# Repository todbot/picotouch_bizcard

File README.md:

# picotouch_bizcard

Business card-sized (2"x1.5") USB / MIDI touch controller

video demo on youtube: https://www.youtube.com/watch?v=1QFjxGo58Xc

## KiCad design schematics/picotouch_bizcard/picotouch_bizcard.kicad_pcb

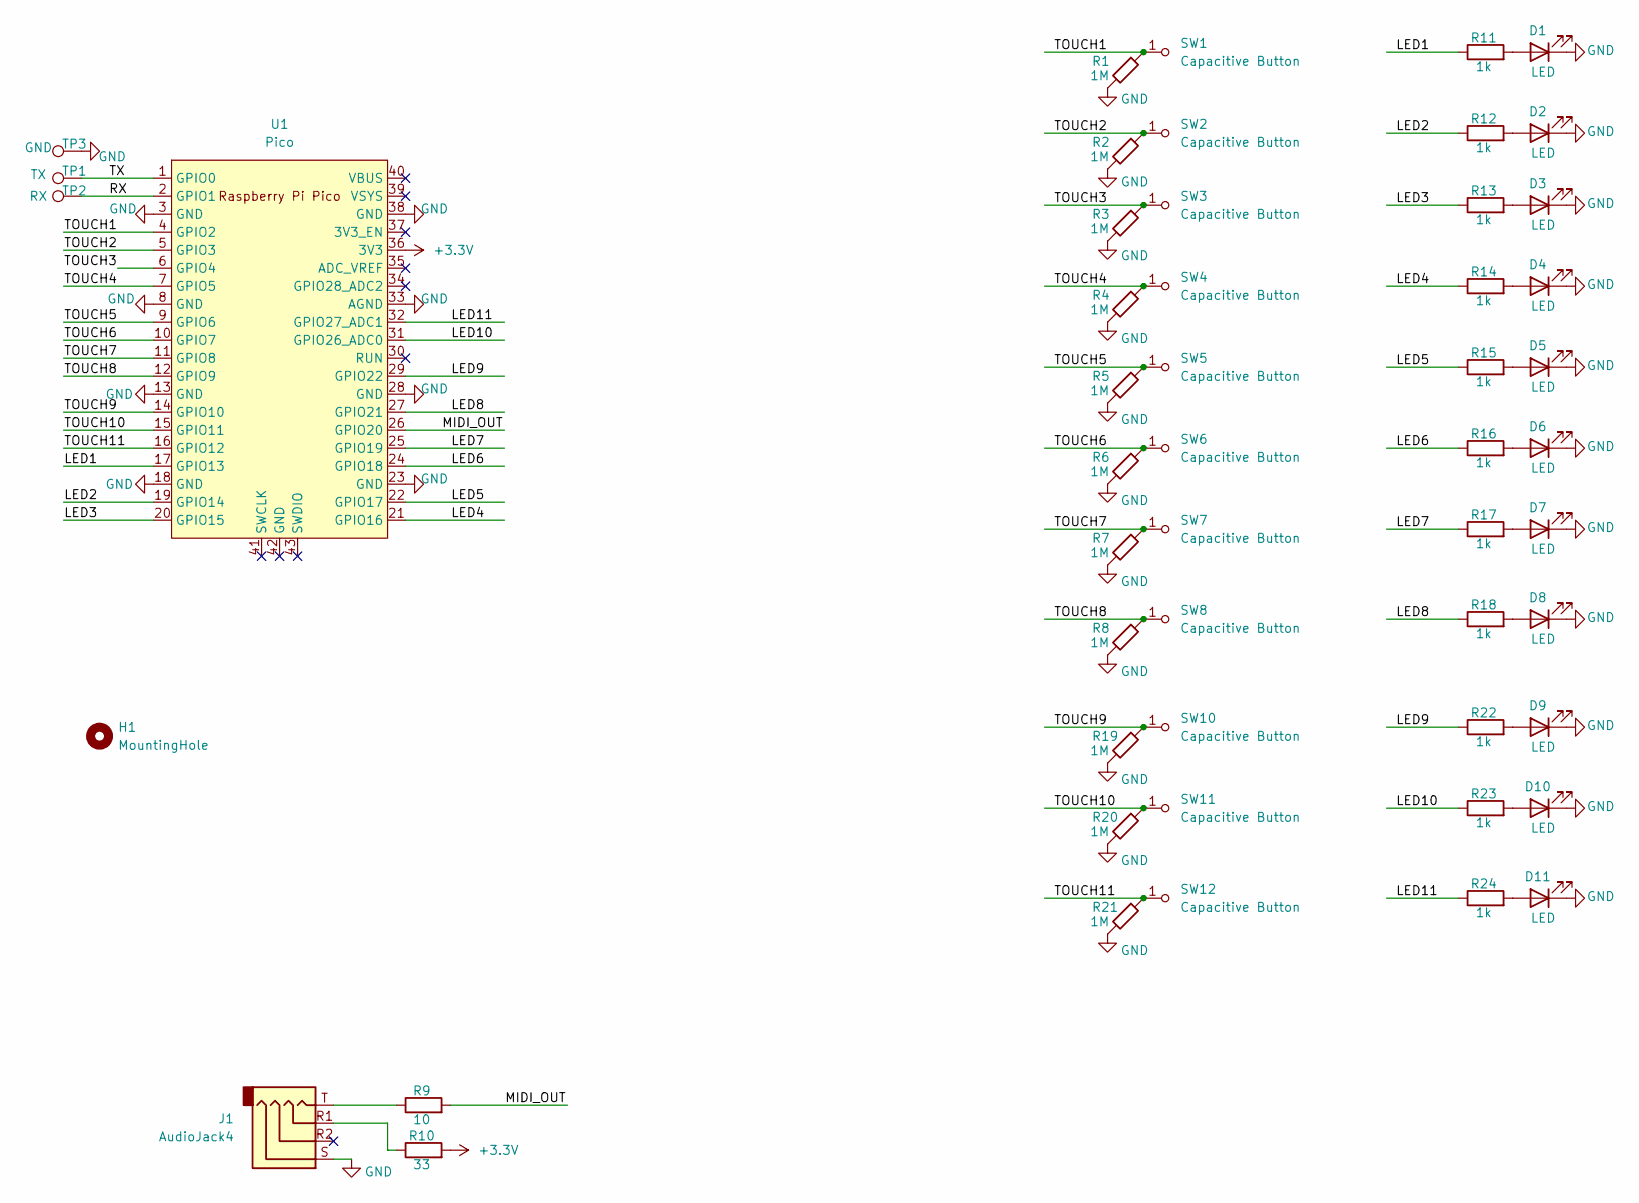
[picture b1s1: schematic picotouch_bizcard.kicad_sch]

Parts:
D1, D2, D3, D4, D5, D6, D7, D8, D9, D10, D11: LED; LED1206_LTST-C230KRKT-cutout; LCSC C125107
H1: MountingHole; MountingHole_2.5mm
J1: AudioJack4; Jack_3.5mm_PJ320D_Horizontal
R1, R2, R3, R4, R5, R6, R7, R8, R19, R20, R21: 1M; R_0603_1608Metric
R9: 10; R_0603_1608Metric
R10: 33; R_0603_1608Metric
R11, R12, R13, R14, R15, R16, R17, R18, R22, R23, R24: 1k; R_0603_1608Metric
SW1, SW2, SW3, SW4, SW5, SW6, SW7, SW8, SW10, SW11, SW12: Capacitive Button; Pad-CapacitiveTouch
TP1: TX; TestPoint_Pad_D2.0mm
TP2: RX; TestPoint_Pad_D2.0mm
TP3: GND; TestPoint_Pad_D2.0mm
U1: Pico; RPi_Pico_SMD

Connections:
+3.3V: R10.2, U1.36 (3V3)
/LED1: R11.1, U1.17 (GPIO13)
/LED2: R12.1, U1.19 (GPIO14)
/LED3: R13.1, U1.20 (GPIO15)
/LED4: R14.1, U1.21 (GPIO16)
/LED5: R15.1, U1.22 (GPIO17)
/LED6: R16.1, U1.24 (GPIO18)
/LED7: R17.1, U1.25 (GPIO19)
/LED8: R18.1, U1.27 (GPIO21)
/LED9: R22.1, U1.29 (GPIO22)
/LED10: R23.1, U1.31 (GPIO26_ADC0)
/LED11: R24.1, U1.32 (GPIO27_ADC1)
/MIDI_OUT: R9.2, U1.26 (GPIO20)
/RX: TP2.1, U1.2 (GPIO1)
/TOUCH1: R1.1, SW1.1 (A), U1.4 (GPIO2)
/TOUCH2: R2.1, SW2.1 (A), U1.5 (GPIO3)
/TOUCH3: R3.1, SW3.1 (A), U1.6 (GPIO4)
/TOUCH4: R4.1, SW4.1 (A), U1.7 (GPIO5)
/TOUCH5: R5.1, SW5.1 (A), U1.9 (GPIO6)
/TOUCH6: R6.1, SW6.1 (A), U1.10 (GPIO7)
/TOUCH7: R7.1, SW7.1 (A), U1.11 (GPIO8)
/TOUCH8: R8.1, SW8.1 (A), U1.12 (GPIO9)
/TOUCH9: R19.1, SW10.1 (A), U1.14 (GPIO10)
/TOUCH10: R20.1, SW11.1 (A), U1.15 (GPIO11)
/TOUCH11: R21.1, SW12.1 (A), U1.16 (GPIO12)
/TX: TP1.1, U1.1 (GPIO0)
GND: D1.1 (K), D2.1 (K), D3.1 (K), D4.1 (K), D5.1 (K), D6.1 (K), D7.1 (K), D8.1 (K), D9.1 (K), D10.1 (K), D11.1 (K), J1.S, R1.2, R2.2, R3.2, R4.2, R5.2, R6.2, R7.2, R8.2, R19.2, R20.2, R21.2, TP3.1, U1.3 (GND), U1.8 (GND), U1.13 (GND), U1.18 (GND), U1.23 (GND), U1.28 (GND), U1.33 (AGND), U1.38 (GND)
unnamed: D1.2 (A), R11.2
unnamed: D2.2 (A), R12.2
unnamed: D3.2 (A), R13.2
unnamed: D4.2 (A), R14.2
unnamed: D5.2 (A), R15.2
unnamed: D6.2 (A), R16.2
unnamed: D7.2 (A), R17.2
unnamed: D8.2 (A), R18.2
unnamed: D9.2 (A), R22.2
unnamed: D10.2 (A), R23.2
unnamed: D11.2 (A), R24.2
unnamed: J1.R1, R10.1
unnamed: J1.T, R9.1

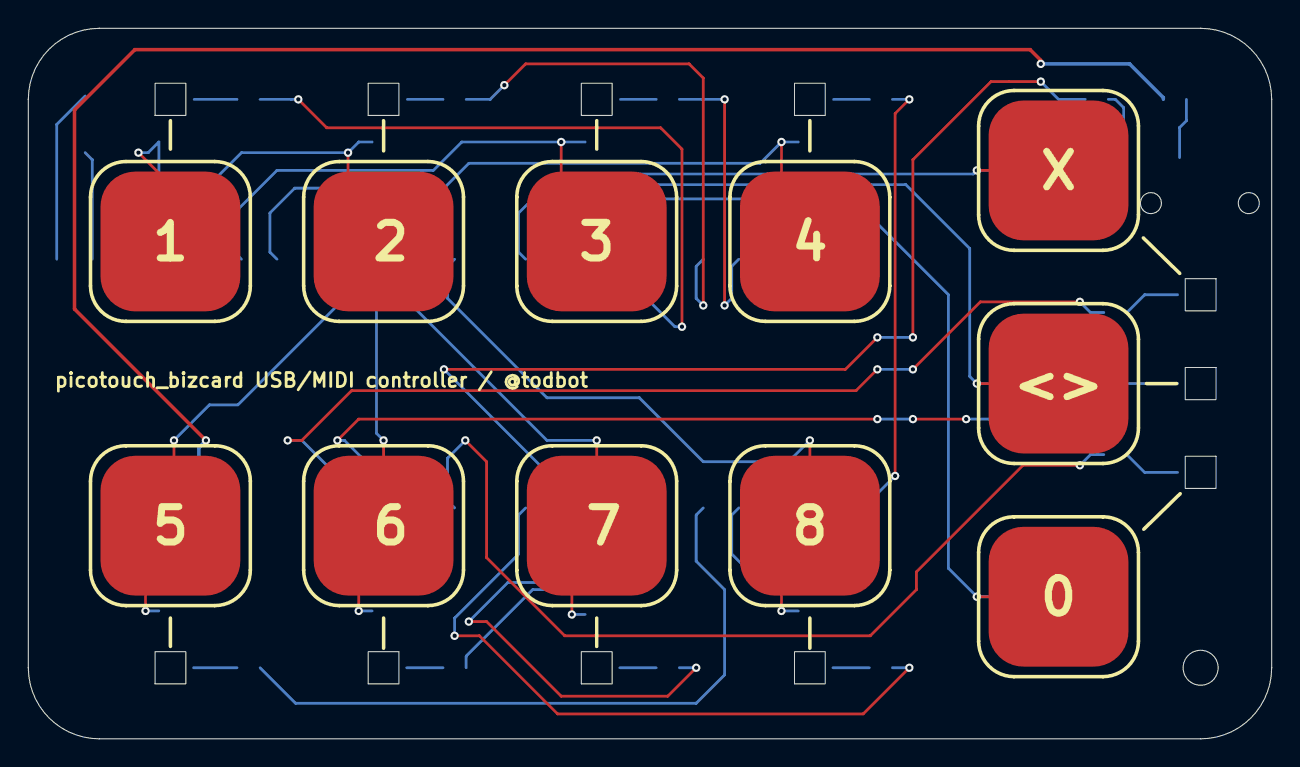
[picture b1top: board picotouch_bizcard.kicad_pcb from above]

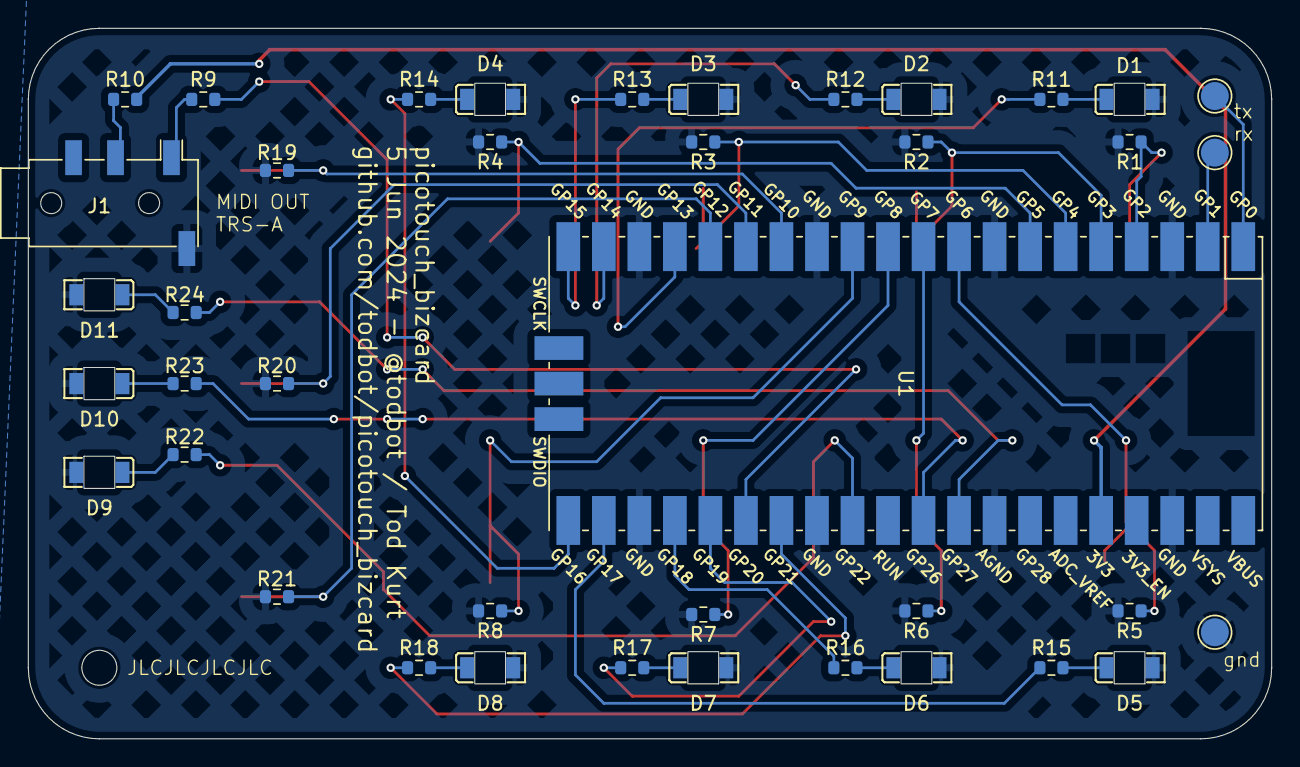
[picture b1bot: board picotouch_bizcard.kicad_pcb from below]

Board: 2 copper layers, 88.9 x 50.8 mm, 52 parts (40 on the bottom side), 40 nets.

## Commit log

2024-06-06 add cirpy dir
2024-06-06 fully routed
2024-06-06 silkscreen
2024-06-06 added tx/rx test points and mounting hole
2024-06-07 submit to fab
2024-06-13 add some circuitpython examples
2024-06-13 add link to tmidi
